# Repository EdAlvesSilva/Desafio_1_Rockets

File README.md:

# Desafio_1_Rockets

Arquivos relativos ao desafio 1 do processo seletivo da equipe Minerva Rockets

detonador.sch -> Esquemático do detonador
detonador.brd -> Arquivo .brd do detonador

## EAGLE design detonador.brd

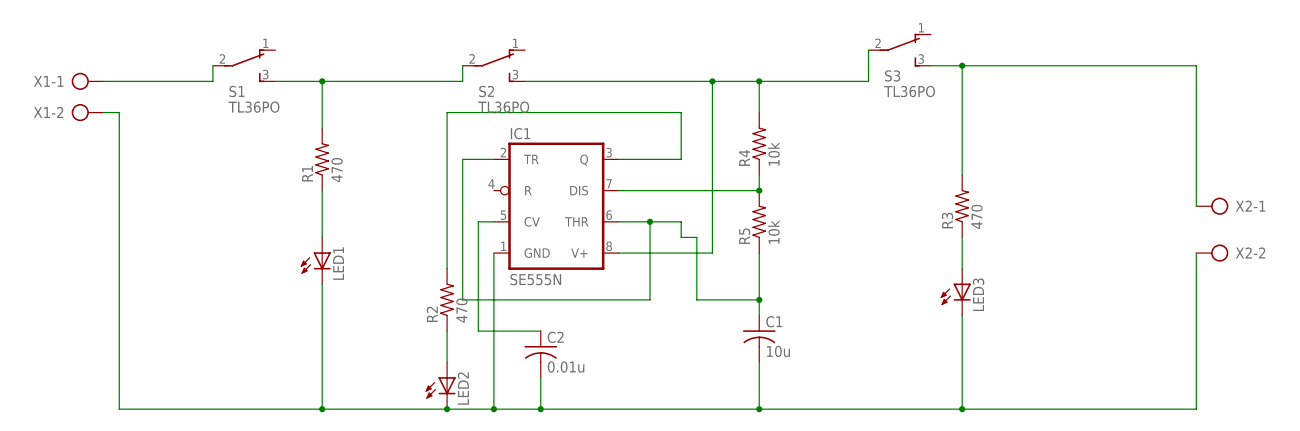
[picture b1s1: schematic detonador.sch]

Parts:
C1: 10u; C025-040X050
C2: 0.01u; C025-040X050
IC1: SE555N; DIL08-ROUND
LED1, LED2, LED3: LED5MM
R1, R2, R3: 470; 0207/12
R4, R5: 10k; 0207/10
S1, S2, S3: TL36PO; TL3XPO
X1, X2: AK500/2-H

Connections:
unnamed: S1.2, X1.1
unnamed: R1.2, S1.3 (S), S2.2
unnamed: IC1.8 (V+), R4.2, S2.3 (S), S3.2
unnamed: LED1.A, R1.1
unnamed: LED2.A, R2.1
unnamed: C1.2, C2.2, IC1.1 (GND), LED1.K (C), LED2.K (C), LED3.K (C), X1.2, X2.2
unnamed: LED3.A, R3.1
unnamed: R3.2, S3.3 (S), X2.1
unnamed: IC1.3 (Q), R2.2
unnamed: C1.1, IC1.2 (TR), IC1.6 (THR), R5.1
unnamed: C2.1, IC1.5 (CV)
unnamed: IC1.7 (DIS), R4.1, R5.2

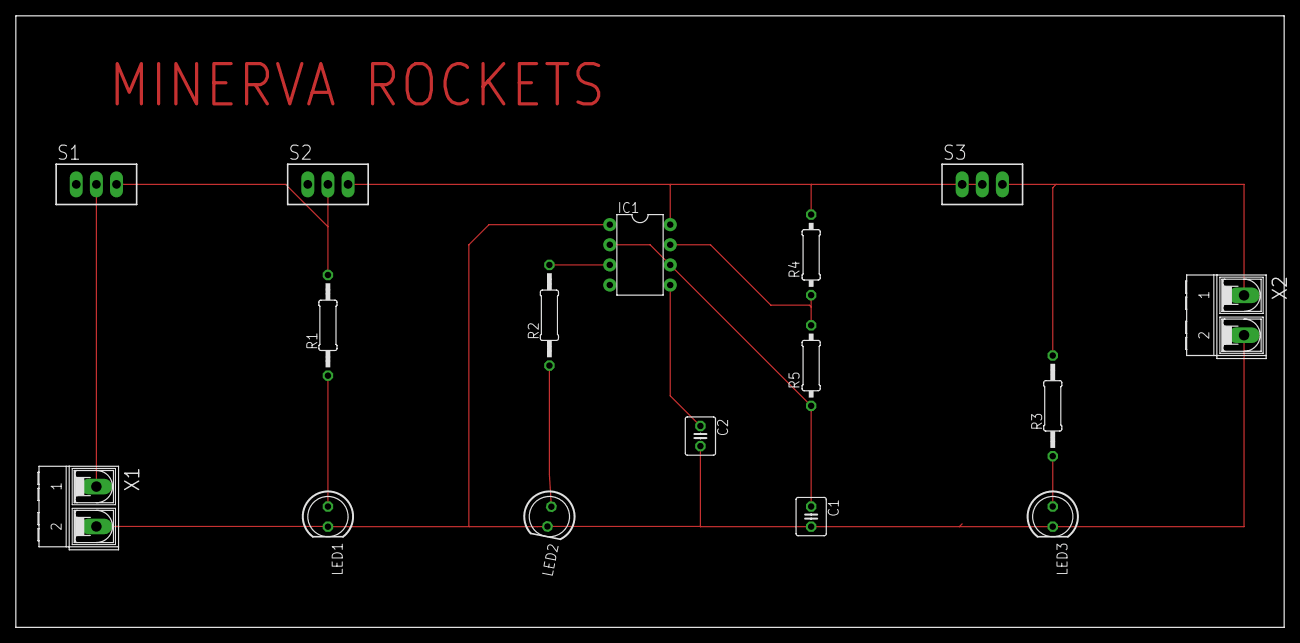
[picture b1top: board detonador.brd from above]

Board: 2 copper layers, 160.0 x 77.1 mm, 16 parts (0 on the bottom side), 12 nets.

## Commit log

2017-07-31 Files + Description
    Adicionados os arquivos e a descrição no README
2017-07-31 Edicao no README
